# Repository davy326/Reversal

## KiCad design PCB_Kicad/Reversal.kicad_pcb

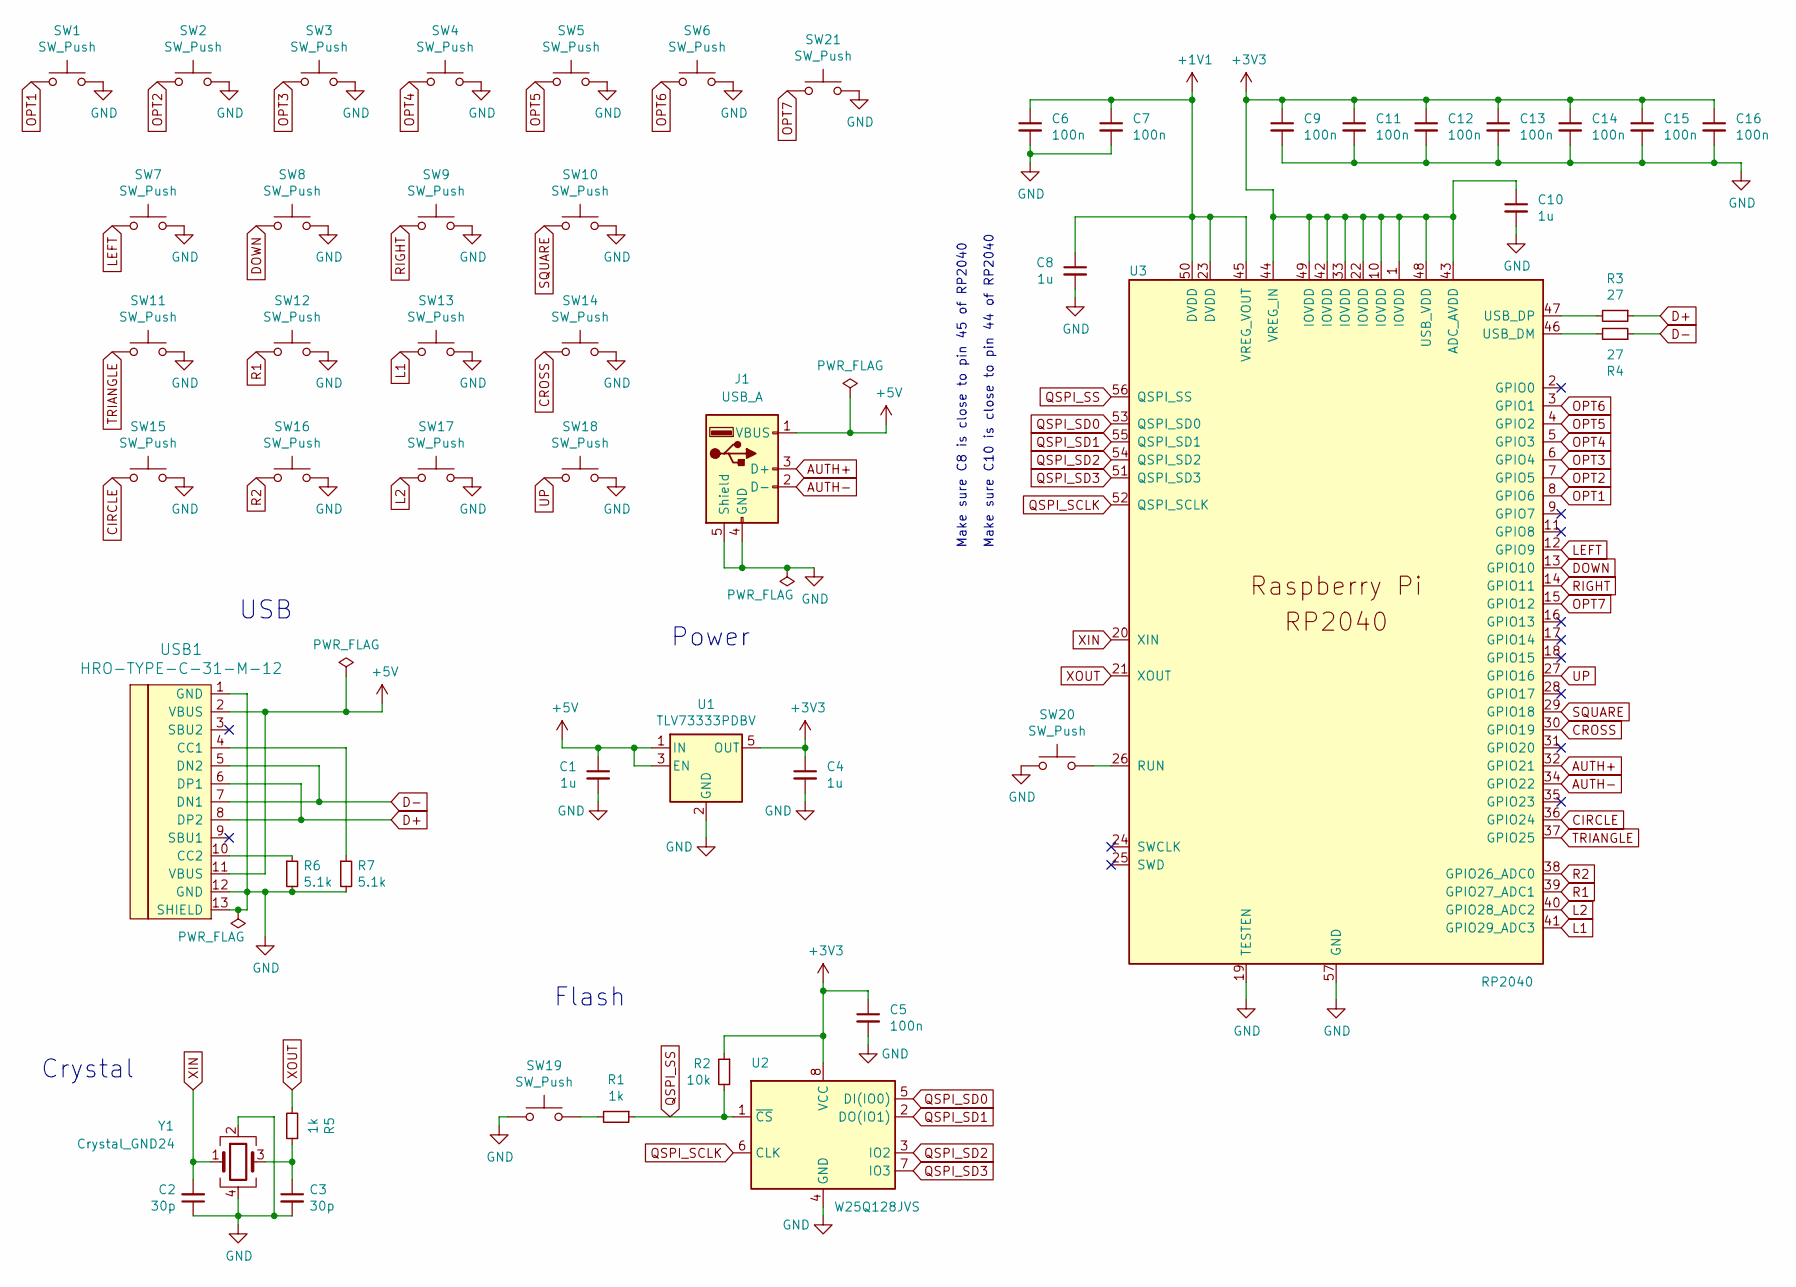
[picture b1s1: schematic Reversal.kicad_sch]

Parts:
C1, C4, C8, C10: 1u; C_0402_1005Metric; LCSC C52923
C2, C3: 30p; C_0402_1005Metric; LCSC C1570
C5, C6, C7, C9, C11, C12, C13, C14, C15, C16: 100n; C_0402_1005Metric; LCSC C1525
J1: USB_A; USB-A-TH_C42425; LCSC C42425
R1, R5: 1k; R_0402_1005Metric; LCSC C11702
R2: 10k; R_0402_1005Metric; LCSC C25744
R3, R4: 27; R_0402_1005Metric; LCSC C138021
R6, R7: 5.1k; R_0402_1005Metric; LCSC C25905
SW1, SW2, SW3, SW4, SW19, SW20, SW21: SW_Push; SW_SPST_Omron_B3FS-100xP; LCSC C271750
SW5, SW6, SW7, SW8, SW9, SW10, SW11, SW12, SW13, SW14, SW15, SW16, SW17, SW18: SW_Push; SW_Hotswap_Kailh_MX; LCSC C2803348
U1: TLV73333PDBV; SOT-23-5; LCSC C134139
U2: W25Q128JVS; SOIC-8_5.23x5.23mm_P1.27mm; LCSC C97521
U3: RP2040; RP2040-QFN-56; LCSC C2040
USB1: HRO-TYPE-C-31-M-12; HRO-TYPE-C-31-M-12-Assembly; LCSC C165948
Y1: Crystal_GND24; Crystal_SMD_3225-4Pin_3.2x2.5mm; LCSC C9002

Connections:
+1V1: C6.1, C7.1, C8.1, U3.23 (DVDD), U3.45 (VREG_VOUT), U3.50 (DVDD)
+3V3: C4.1, C5.1, C9.1, C10.1, C11.1, C12.1, C13.1, C14.1, C15.1, C16.1, R2.1, U1.5 (OUT), U2.8 (VCC), U3.1 (IOVDD), U3.10 (IOVDD), U3.22 (IOVDD), U3.33 (IOVDD), U3.42 (IOVDD), U3.43 (ADC_AVDD), U3.44 (VREG_IN), U3.48 (USB_VDD), U3.49 (IOVDD)
+5V: C1.1, J1.1 (VBUS), U1.1 (IN), U1.3 (EN), USB1.2 (VBUS), USB1.11 (VBUS)
AUTH+: J1.3 (D+), U3.32 (GPIO21)
AUTH-: J1.2 (D-), U3.34 (GPIO22)
CIRCLE: SW15.1, U3.36 (GPIO24)
CROSS: SW14.1, U3.30 (GPIO19)
D+: R3.1, USB1.6 (DP1), USB1.8 (DP2)
D-: R4.1, USB1.5 (DN2), USB1.7 (DN1)
DOWN: SW8.1, U3.13 (GPIO10)
GND: C1.2, C2.1, C3.2, C4.2, C5.2, C6.2, C7.2, C8.2, C9.2, C10.2, C11.2, C12.2, C13.2, C14.2, C15.2, C16.2, J1.4 (GND), J1.5 (Shield), R6.2, R7.2, SW1.2, SW2.2, SW3.2, SW4.2, SW5.2, SW6.2, SW7.2, SW8.2, SW9.2, SW10.2, SW11.2, SW12.2, SW13.2, SW14.2, SW15.2, SW16.2, SW17.2, SW18.2, SW19.1, SW20.1, SW21.2, U1.2 (GND), U2.4 (GND), U3.19 (TESTEN), U3.57 (GND), USB1.1 (GND), USB1.12 (GND), USB1.13 (SHIELD), Y1.2, Y1.4
L1: SW13.1, U3.41 (GPIO29_ADC3)
L2: SW17.1, U3.40 (GPIO28_ADC2)
LEFT: SW7.1, U3.12 (GPIO9)
unnamed: C3.1, R5.1, Y1.3
unnamed: R1.2, SW19.2
unnamed: SW20.2, U3.26 (RUN)
unnamed: R4.2, U3.46 (USB_DM)
unnamed: R3.2, U3.47 (USB_DP)
unnamed: R7.1, USB1.4 (CC1)
unnamed: R6.1, USB1.10 (CC2)
OPT1: SW1.1, U3.8 (GPIO6)
OPT2: SW2.1, U3.7 (GPIO5)
OPT3: SW3.1, U3.6 (GPIO4)
OPT4: SW4.1, U3.5 (GPIO3)
OPT5: SW5.1, U3.4 (GPIO2)
OPT6: SW6.1, U3.3 (GPIO1)
OPT7: SW21.1, U3.15 (GPIO12)
QSPI_SCLK: U2.6 (CLK), U3.52 (QSPI_SCLK)
QSPI_SD0: U2.5 (DI(IO0)), U3.53 (QSPI_SD0)
QSPI_SD1: U2.2 (DO(IO1)), U3.55 (QSPI_SD1)
QSPI_SD2: U2.3 (IO2), U3.54 (QSPI_SD2)
QSPI_SD3: U2.7 (IO3), U3.51 (QSPI_SD3)
QSPI_SS: R1.1, R2.2, U2.1 (~CS), U3.56 (QSPI_SS)
R1: SW12.1, U3.39 (GPIO27_ADC1)
R2: SW16.1, U3.38 (GPIO26_ADC0)
RIGHT: SW9.1, U3.14 (GPIO11)
SQUARE: SW10.1, U3.29 (GPIO18)
TRIANGLE: SW11.1, U3.37 (GPIO25)
UP: SW18.1, U3.27 (GPIO16)
XIN: C2.2, U3.20 (XIN), Y1.1
XOUT: R5.2, U3.21 (XOUT)

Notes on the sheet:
Make sure C10 is close to pin 44 of RP2040
Power
Crystal
Make sure C8 is close to pin 45 of RP2040
Flash
USB

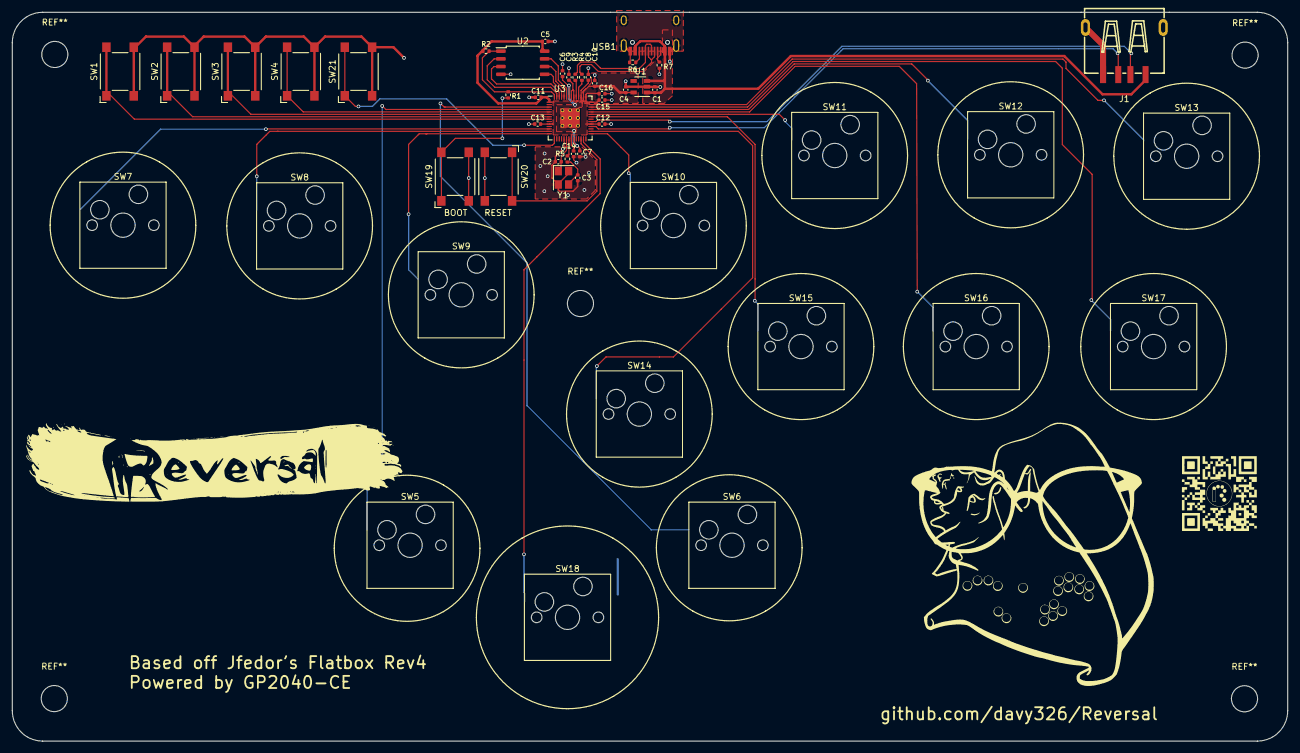
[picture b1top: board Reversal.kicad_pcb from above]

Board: 2 copper layers, 210.0 x 120.0 mm, 50 parts (0 on the bottom side), 42 nets.

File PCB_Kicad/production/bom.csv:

Designator,Footprint,Quantity,Value,LCSC Part #
"C1, C10, C4, C8",0402,4,1u,C52923
"C11, C12, C13, C14, C15, C16, C5, C6, C7, C9",0402,10,100n,C1525
"C2, C3",0402,2,30p,C1570
J1,USB-A-TH_C42425,1,USB_A,C42425
"R1, R5",0402,2,1k,C11702
R2,0402,1,10k,C25744
"R3, R4",0402,2,27,C138021
"R6, R7",0402,2,5.1k,C25905
"SW1, SW19, SW2, SW20, SW21, SW3, SW4",SW_SPST_Omron_B3FS-100xP,7,SW_Push,C271750
"SW10, SW11, SW12, SW13, SW14, SW15, SW16, SW17, SW18, SW5, SW6, SW7, SW8, SW9",SW_Hotswap_Kailh_MX,14,SW_Push,C2803348
U1,SOT-23-5,1,TLV73333PDBV,C134139
U2,SOIC-8_5.23x5.23mm_P1.27mm,1,W25Q128JVS,C97521
U3,RP2040-QFN-56,1,RP2040,C2040
USB1,HRO-TYPE-C-31-M-12-Assembly,1,HRO-TYPE-C-31-M-12,C165948
Y1,Crystal_SMD_3225-4Pin_3.2x2.5mm,1,Crystal_GND24,C9002

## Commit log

2024-06-03 Getting basic repo setup
2024-06-21 initial pcb
2024-07-04 Initial push with stuff
